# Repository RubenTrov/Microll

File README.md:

This is going to be a small PCB with a microcontroller, IMU and a form of wirelessly transmitting that information though wifi/bluetooh.
It will serve as a central piece for a lot of future IoT projects.

#How to program the PCB
This board has two microcontrollers that share the Same USB Port through a switch.
##Programming the STM32
1. The USB selector switch should be flipped to the SM32 position.
2. Open STM32CubeIDE and load the file that you wish to flash to the microcontroller.
3. Set the Boot pin High by setting the Boot on the DIP switch to position 2 and then from the ON side of the switch connect a jumper to the 3.3V GPIO header.
4. Connect the USB to the PCB to power on the board. This should make the STM32 be detected by the programmer.
5. Erase the memory and upload the file.
6. Disconnect the PCB from the USB and switch the position of Boot on the DIP switch.
7. Plug the USB back in the PCB and it will begin executing the program that was uploaded!

##Programming the ESP32
1. You may need to connect the GPIO0 pin to GND using a jumper cable before powering on the board
2. Flip the USB switch to the ESP32 position
3. Flip the EN on the DIP switch to the on position to connect it to 3.3V
4. Power on the board by plugging in the USB
5. Disconnect the GPIO0 pin from GND
6. The board should now be ready to program. Use the editor of your choice for this.

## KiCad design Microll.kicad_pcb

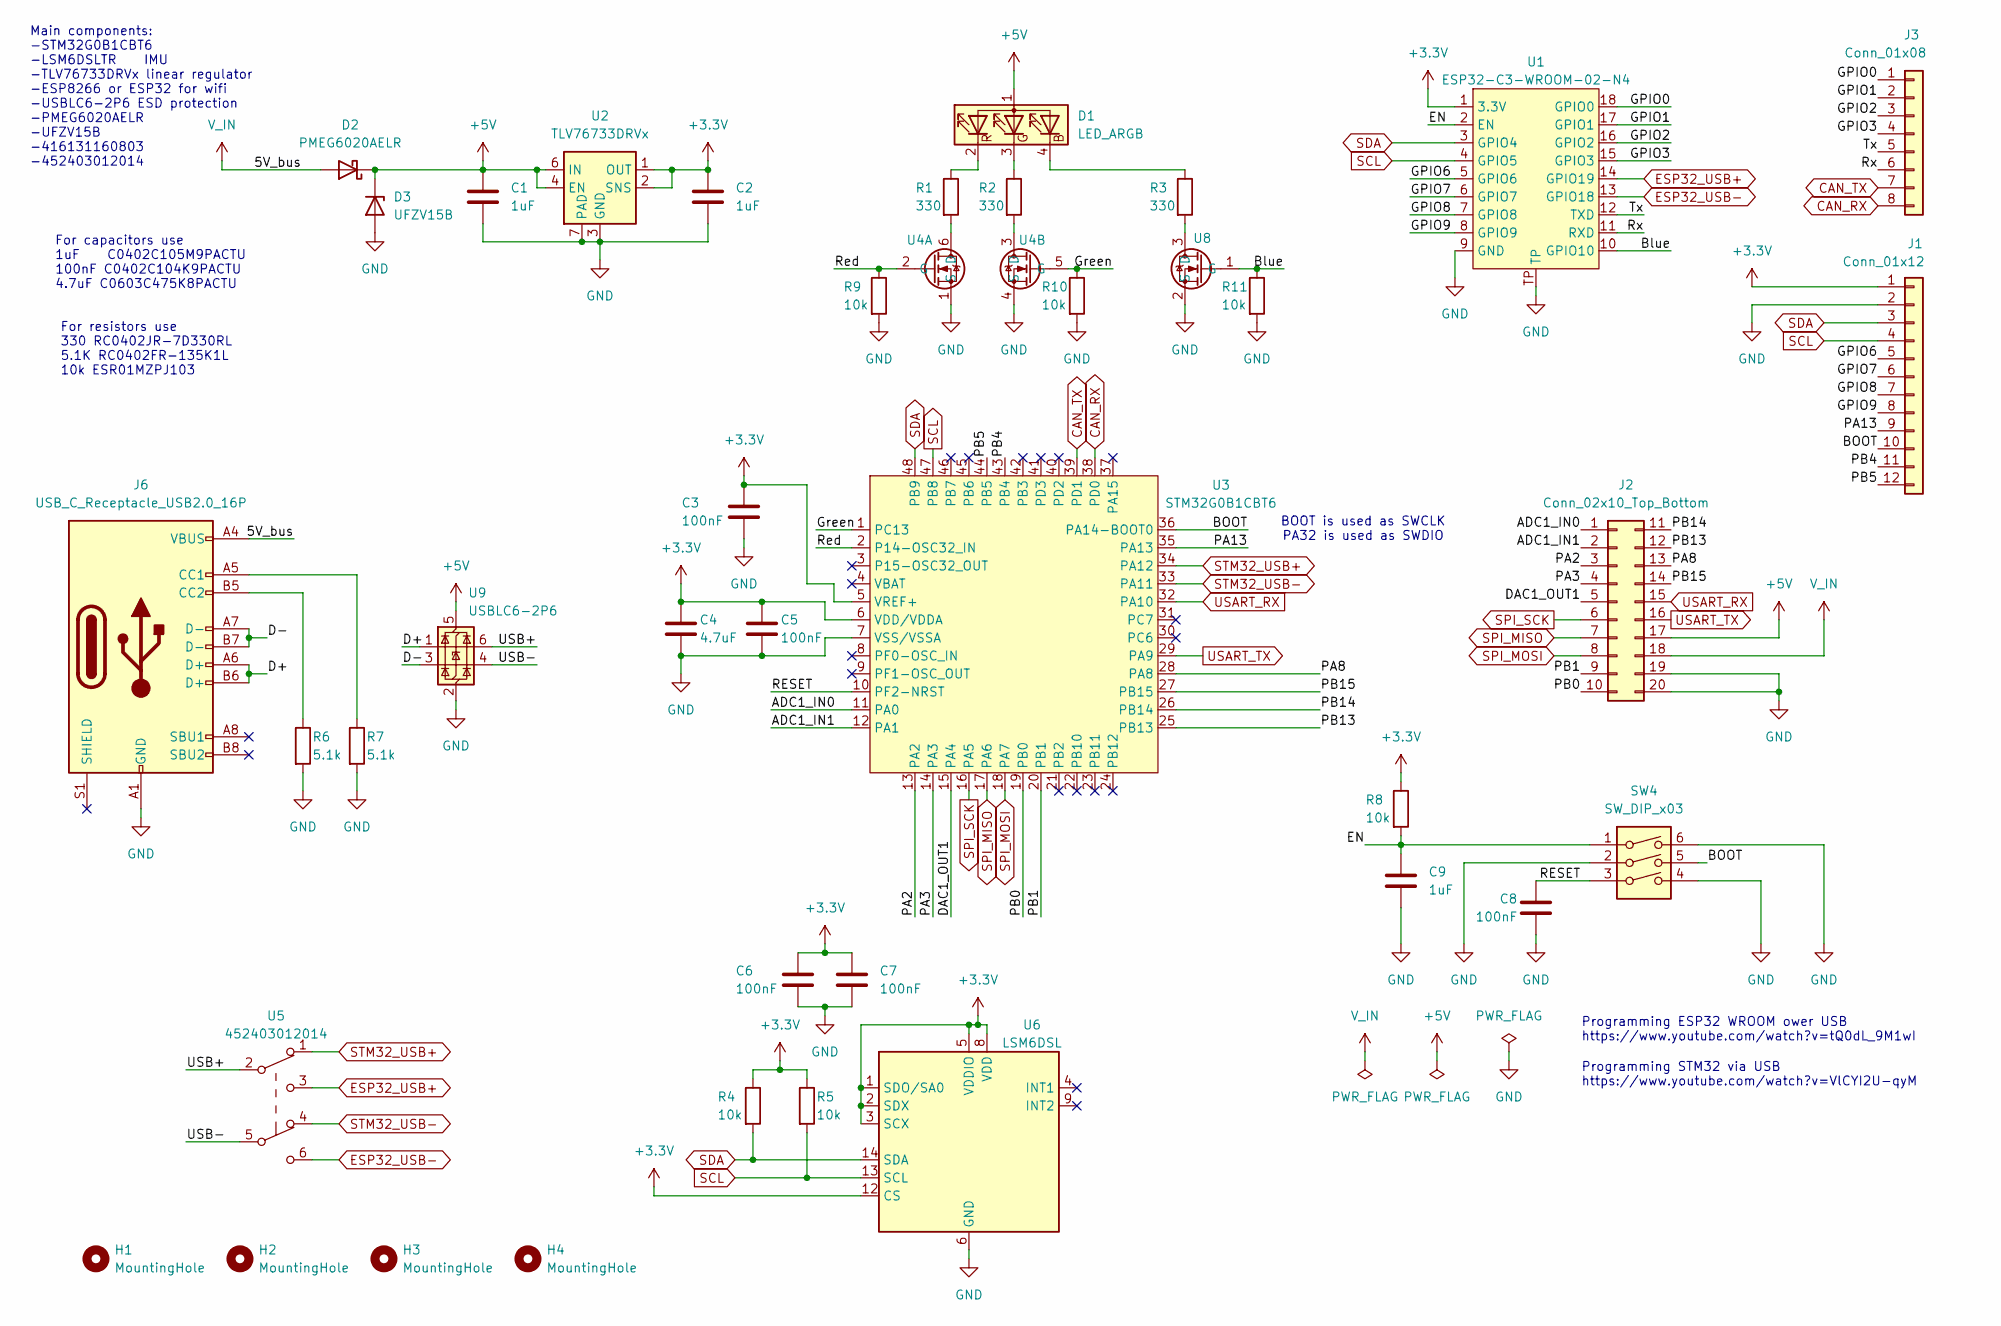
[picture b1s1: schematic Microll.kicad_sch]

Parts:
C1, C2, C9: 1uF; C_0402_1005Metric
C3, C5, C6, C7, C8: 100nF; C_0402_1005Metric
C4: 4.7uF; C_0603_1608Metric
D1: LED_ARGB; APTF1616LSEEZGKQBKC
D2: PMEG6020AELR; D_SOD-123
D3: UFZV15B; D_SOD-323F
H1, H2, H3, H4: MountingHole; MountingHole_2.2mm_M2
J1: Conn_01x12; PinSocket_1x12_P2.54mm_Vertical
J2: Conn_02x10_Top_Bottom; PinSocket_2x10_P2.54mm_Vertical
J3: Conn_01x08; PinSocket_1x08_P2.54mm_Vertical
J6: USB_C_Receptacle_USB2.0_16P; USB_C_Receptacle_GCT_USB4105-xx-A_16P_TopMnt_Horizontal
R1, R2, R3: 330; R_0402_1005Metric
R4, R5, R8, R9, R10, R11: 10k; R_0402_1005Metric
R6, R7: 5.1k; R_0402_1005Metric
SW4: SW_DIP_x03; WE_DIP_SWITCH_3_POS
U1: ESP32-C3-WROOM-02-N4
U2: TLV76733DRVx; WSON-6-1EP_2x2mm_P0.65mm_EP1x1.6mm_ThermalVias
U3: STM32G0B1CBT6; LQFP-48_7x7mm_P0.5mm
U4: BSD235NH6327XTSA1; SOT-363_SC-70-6
U5: 452403012014; DPDT_Switch_x2
U6: LSM6DSL; LGA-14_3x2.5mm_P0.5mm_LayoutBorder3x4y
U8: NX7002AKW,115; SOT-323_SC-70
U9: USBLC6-2P6; SOT-666

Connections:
+3.3V: C2.1, C3.1, C4.1, C5.1, C6.1, C7.1, J1.1, R4.1, R5.1, R8.1, U1.1 (3.3V), U2.1 (OUT), U2.2 (SNS), U3.5 (VREF+), U3.6 (VDD/VDDA), U6.1 (SDO/SA0), U6.2 (SDX), U6.3 (SCX), U6.5 (VDDIO), U6.8 (VDD), U6.12 (CS)
+5V: C1.1, D1.1 (A), D2.1 (K), D3.1 (K), J2.17, U2.4 (EN), U2.6 (IN), U9.5 (VBUS)
/ADC1_IN0: J2.1, U3.11 (PA0)
/ADC1_IN1: J2.2, U3.12 (PA1)
/BOOT: J1.10, SW4.5, U3.36 (PA14-BOOT0)
/Blue: R11.1, U1.10 (GPIO10), U8.1 (G)
/D+: J6.A6 (D+), J6.B6 (D+), U9.1 (I/O1)
/D-: J6.A7 (D-), J6.B7 (D-), U9.3 (I/O2)
/DAC1_OUT1: J2.5, U3.15 (PA4)
/EN: C9.1, R8.2, SW4.1, U1.2 (EN)
/GPIO0: J3.1, U1.18 (GPIO0)
/GPIO1: J3.2, U1.17 (GPIO1)
/GPIO2: J3.3, U1.16 (GPIO2)
/GPIO3: J3.4, U1.15 (GPIO3)
/GPIO6: J1.5, U1.5 (GPIO6)
/GPIO7: J1.6, U1.6 (GPIO7)
/GPIO8: J1.7, U1.7 (GPIO8)
/GPIO9: J1.8, U1.8 (GPIO9)
/Green: R10.1, U3.1 (PC13), U4.5 (G)
/PA2: J2.3, U3.13 (PA2)
/PA3: J2.4, U3.14 (PA3)
/PA8: J2.13, U3.28 (PA8)
/PA13: J1.9, U3.35 (PA13)
/PB0: J2.10, U3.19 (PB0)
/PB1: J2.9, U3.20 (PB1)
/PB4: J1.11, U3.43 (PB4)
/PB5: J1.12, U3.44 (PB5)
/PB13: J2.12, U3.25 (PB13)
/PB14: J2.11, U3.26 (PB14)
/PB15: J2.14, U3.27 (PB15)
/RESET: C8.1, SW4.3, U3.10 (PF2-NRST)
/Red: R9.1, U3.2 (P14-OSC32_IN), U4.2 (G)
/Rx: J3.6, U1.11 (RXD)
/Tx: J3.5, U1.12 (TXD)
/USB+: U5.2, U9.6 (I/O1)
/USB-: U5.5, U9.4 (I/O2)
CAN_RX: J3.8, U3.38 (PD0)
CAN_TX: J3.7, U3.39 (PD1)
ESP32_USB+: U1.14 (GPIO19), U5.3
ESP32_USB-: U1.13 (GPIO18), U5.6
GND: C1.2, C2.2, C3.2, C4.2, C5.2, C6.2, C7.2, C8.2, C9.2, D3.2 (A), J1.2, J2.19, J2.20, J6.A1 (GND), J6.A12 (GND), J6.B1 (GND), J6.B12 (GND), R6.2, R7.2, R9.2, R10.2, R11.2, SW4.2, SW4.4, SW4.6, U1.9 (GND), U1.TP, U2.3 (GND), U2.5 (GND), U2.7 (PAD), U3.7 (VSS/VSSA), U4.1 (S), U4.4 (S), U6.6 (GND), U6.7 (GND), U8.2 (S), U9.2 (GND)
unnamed: D1.4 (BK), R3.1
unnamed: D1.3 (GK), R2.1
unnamed: D1.2 (RK), R1.1
unnamed: J6.A5 (CC1), R7.1
unnamed: J6.B5 (CC2), R6.1
unnamed: R1.2, U4.6 (D)
unnamed: R2.2, U4.3 (D)
unnamed: R3.2, U8.3 (D)
SCL: J1.4, R5.2, U1.4 (GPIO5), U3.47 (PB8), U6.13 (SCL)
SDA: J1.3, R4.2, U1.3 (GPIO4), U3.48 (PB9), U6.14 (SDA)
SPI_MISO: J2.7, U3.17 (PA6)
SPI_MOSI: J2.8, U3.18 (PA7)
SPI_SCK: J2.6, U3.16 (PA5)
STM32_USB+: U3.34 (PA12), U5.1
STM32_USB-: U3.33 (PA11), U5.4
USART_RX: J2.15, U3.32 (PA10)
USART_TX: J2.16, U3.29 (PA9)
V_IN: D2.2 (A), J2.18, J6.A4 (VBUS), J6.A9 (VBUS), J6.B4 (VBUS), J6.B9 (VBUS)

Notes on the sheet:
Programming ESP32 WROOM ower USB https://www.youtube.com/watch?v=tQ0dL_9M1wI
Programming STM32 via USB https://www.youtube.com/watch?v=VlCYI2U-qyM
For capacitors use 1uF C0402C105M9PACTU 100nF C0402C104K9PACTU 4.7uF C0603C475K8PACTU
BOOT is used as SWCLK PA32 is used as SWDIO
Main components: -STM32G0B1CBT6 -LSM6DSLTR IMU -TLV76733DRVx linear regulator -ESP8266 or ESP32 for wifi -USBLC6-2P6 ESD protection -PMEG6020AELR -UFZV15B -416131160803 -452403012014
For resistors use 330 RC0402JR-7D330RL 5.1K RC0402FR-135K1L 10k ESR01MZPJ103

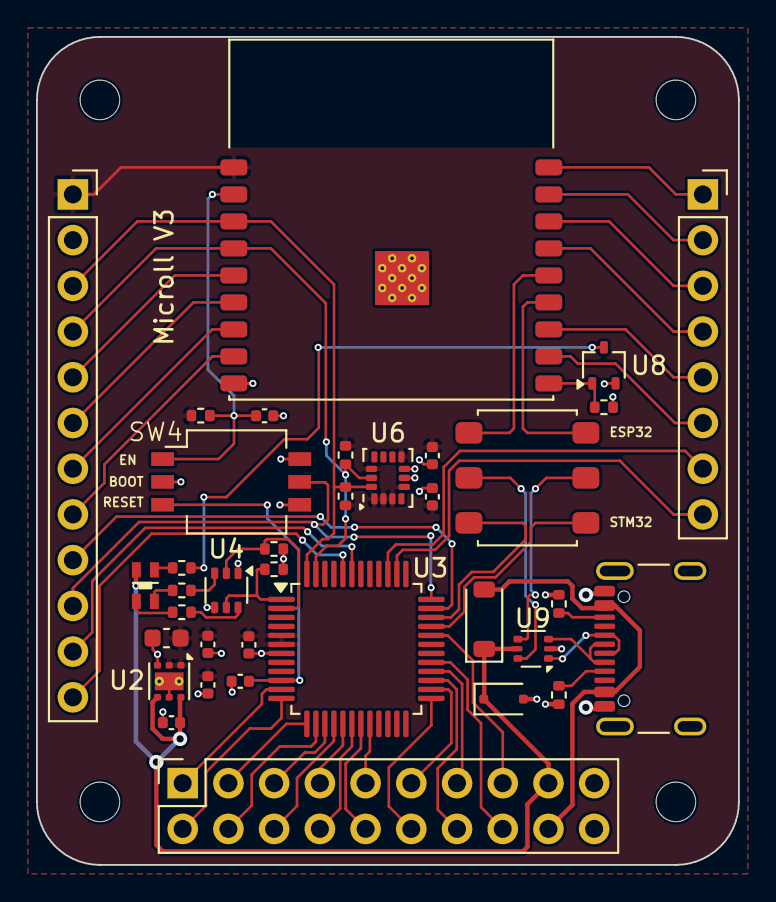
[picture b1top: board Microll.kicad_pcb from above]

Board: 2 copper layers, 39.0 x 46.0 mm, 40 parts (0 on the bottom side), 59 nets.

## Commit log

2023-09-10 Initial project creation
2023-09-10 Initial part selection
2023-09-11 More motes on the board main components.
2023-09-17 something
2023-09-17 Created ESP32, partially drawn footprint
2023-09-17 Finished footprint for ESP32
2023-09-17 gitignoew update
2023-09-17 Added linear regulator symbol and footprint.
2023-09-24 Decided on STM32 microcontroller and made footprint and symbol
2023-09-25 Added IMU. Initial placement of components on PCB to check spacing
2023-09-27 Added some notes on programming the STM32 and ESP32 over USB. Added datasheets to all components.
2023-10-01 Begun drafting linear regulator circuit and passive components
2023-10-01 Thinking of swapping out linear regulator. Thinking about programming jumper to swap between microcontrollers
2023-10-03 Changed linear regulator to TLV767
2023-10-03 added some capacitors to the IMU
2023-10-07 Added 3D models to all PCB components. Added switch for USB programming between microcontrollers
2023-10-07 Added todo list
2023-10-10 Corrected mistake in usb wiring to switch
2023-10-10 Added ESD protection, decoupling capacitors and new footprints
2023-10-15 Added an RGB LED and solder jumpers for the EN and Boot pins of the microcontrollers in case I need to do something woth programming
2023-10-15 Added nets to the LEDs. Pretty much all that is left in the scematic is adding the I/O pins and then it's off to the PCB layout
2023-11-12 Added I/O connections
2023-12-23 Initial placement for the PCB.
2023-12-25 Updated STMew and ESP32 symbols with correct pins. Need to update USB-C next.
2024-01-13 Updated USB-C receptacle footprint.
2024-01-13 USB-C footprint should now match schematic
2024-01-13 Organised board sape and pin headers.
2024-01-13 Board ready for track routing
2024-01-20 Started routing tracks
2024-01-27 finished routing. Need to clear DRC errors
2024-01-28 Finishhed Microll PCB
2024-01-28 Added 3D model for USB-C. PCB finished!
2024-01-28 PCB finished and ordered
2024-01-28 Added Gerber files
2024-02-16 Lots of notes on what to improve for the next one
2024-02-16 Added 5.1k resistors to USBC for 5V
2024-02-16 Fixed mistake on PA13 mixing it up with the boot button.
2024-02-16 Changed the enable pin for the ESP32 to a button. adding extra row of IO pins
2024-02-16 adding second regulator for input voltage through GPIO
2024-02-17 Added note to simulate reverse polarity protection diode
2024-02-18 It was fine before but now properly following schematic pin recomended for USBLC ESD protection
2024-02-18 corrected big mistake on 3.3V regulator sns pin
2024-02-18 added input protection diodes. starting new pcb layout
2024-02-19 Removed unnecessary 5V regulator
2024-02-19 Changed connectors to two rows to conserve board space. Still considering getting another secondary boltage regulator for powering external motors
2024-02-21 Begun placement for new Microll PCB
2024-02-22 Updated breakout pinout and placement
2024-02-24 Converted to KiCad 8.0
2024-02-25 Changed the programming switches to a more compact dip format to save board space
2024-03-01 Board outline defined. Initial routing comenced
2024-03-01 Additional routing. Need to update power symbols due tto kicad 8. Need to add 4 pins from STM32
2024-03-01 Largely finishhed routing. Need to sort out 3D model for USBC and add silk skreen pin labels to underside of board
2024-03-01 Updated USBC. Just need to add silkscreen to te bottom 12 pin connector and it's done
2024-03-01 Completed Microll V1.0
2024-03-12 Fixed typo on STM32 symbol pinout
2024-03-26 Update README.md
    Updated the images for V1.0
2024-03-26 Updated gitignore to ignore PCB lock. Tidy up schematic notes
2024-03-26 Update README.md
    Cooler 3D picture
2024-03-26 Updated Readme instructions on how to program the ESP32 and STM32.
2024-03-26 Update README.md
    Updated 3D image again
2024-03-26 Update README.md
    Another 3D image update
2024-04-03 Messed up on the boot option pin and didn't connect it to +3.3V on the other side.. Added a note
2024-04-20 updating microcontroller
2024-04-20 SWDIO and SWCLK now accessible through gpio pins. Microcontroller changed to more solder friendly package
2024-04-21 Made Microll V2 and updated Gerber Files
2024-09-02 Realized why I kept killing both the STM32 and ESP32. I stupidly connected the LEDs to 5V and was having the microcontrollers sink that. The micorcontroller pins can only handle 3.6V max. Even with t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
2024-09-03 small notes added on what will be changed. Schematic doc includes revision
2024-09-04 Added NMOS to control the LEDs. Changed the series resistance to set the appropriate current limit for the LEDs. Updated USB ESD protection. Added Simulations folder with LED simulation.
2024-09-05 Updating component documentation
2024-09-07 Added datasheets to components. Ready to proceed with layout update
2024-09-07 Updated PCB to Microll V3
2024-09-07 Updated Gerber files. Added 3D photos and schematic PDF
2024-09-07 Update README.md
    updated image for V3

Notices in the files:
Microll.kicad_pcb:
© Ruben Trovoada
